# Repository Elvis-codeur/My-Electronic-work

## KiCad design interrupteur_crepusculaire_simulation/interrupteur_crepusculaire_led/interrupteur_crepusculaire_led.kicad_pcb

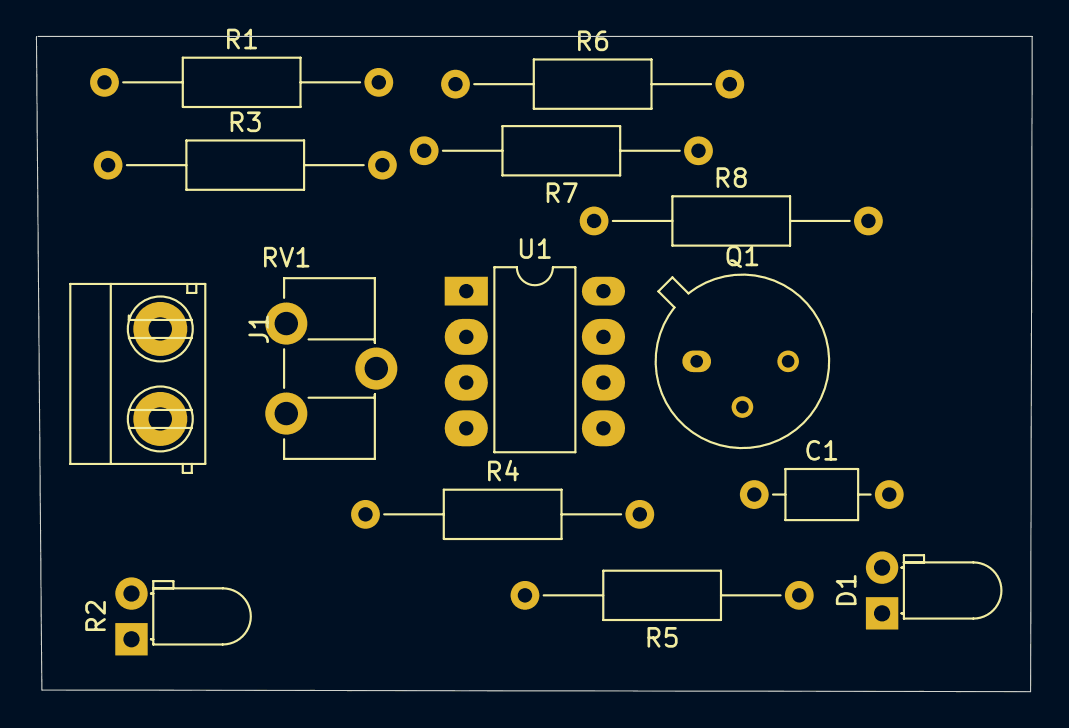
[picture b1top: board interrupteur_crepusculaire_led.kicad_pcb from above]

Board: 2 copper layers, 55.3 x 36.4 mm, 14 parts (0 on the bottom side), 8 nets, no tracks yet.

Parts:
C1: 10nF; C_Axial_L3.8mm_D2.6mm_P7.50mm_Horizontal
D1: LED; LED_D3.0mm_Horizontal_O1.27mm_Z2.0mm
J1: Entrée; Bornier_2pts_L10mm_W8mm_P5mm
Q1: 2N2219; TO-39-3
R1: 10K; R_Axial_DIN0207_L6.3mm_D2.5mm_P15.24mm_Horizontal
R2: LDR03; LED_D3.0mm_Horizontal_O1.27mm_Z2.0mm
R3, R4: 3.3K; R_Axial_DIN0207_L6.3mm_D2.5mm_P15.24mm_Horizontal
R5: 1M; R_Axial_DIN0207_L6.3mm_D2.5mm_P15.24mm_Horizontal
R6: 220R; R_Axial_DIN0207_L6.3mm_D2.5mm_P15.24mm_Horizontal
R7: 2.2K; R_Axial_DIN0207_L6.3mm_D2.5mm_P15.24mm_Horizontal
R8: 560R; R_Axial_DIN0207_L6.3mm_D2.5mm_P15.24mm_Horizontal
RV1: R_POT; Potentiometer_ACP_CA9-H5_Horizontal
U1: LM741; DIP-8_W7.62mm_LongPads

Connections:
GND: C1.2, D1.1, J1.2, R1.2, R2.2, R4.2, R7.2, U1.4
unnamed: Q1.2, R6.1, R7.1
unnamed: Q1.3, R8.2
unnamed: R2.1, U1.3
unnamed: R5.1, R6.2, U1.6
unnamed: RV1.2, U1.2
VCC: C1.1, J1.1, R1.1, R3.1, R8.1, U1.7
vs: D1.2, Q1.1

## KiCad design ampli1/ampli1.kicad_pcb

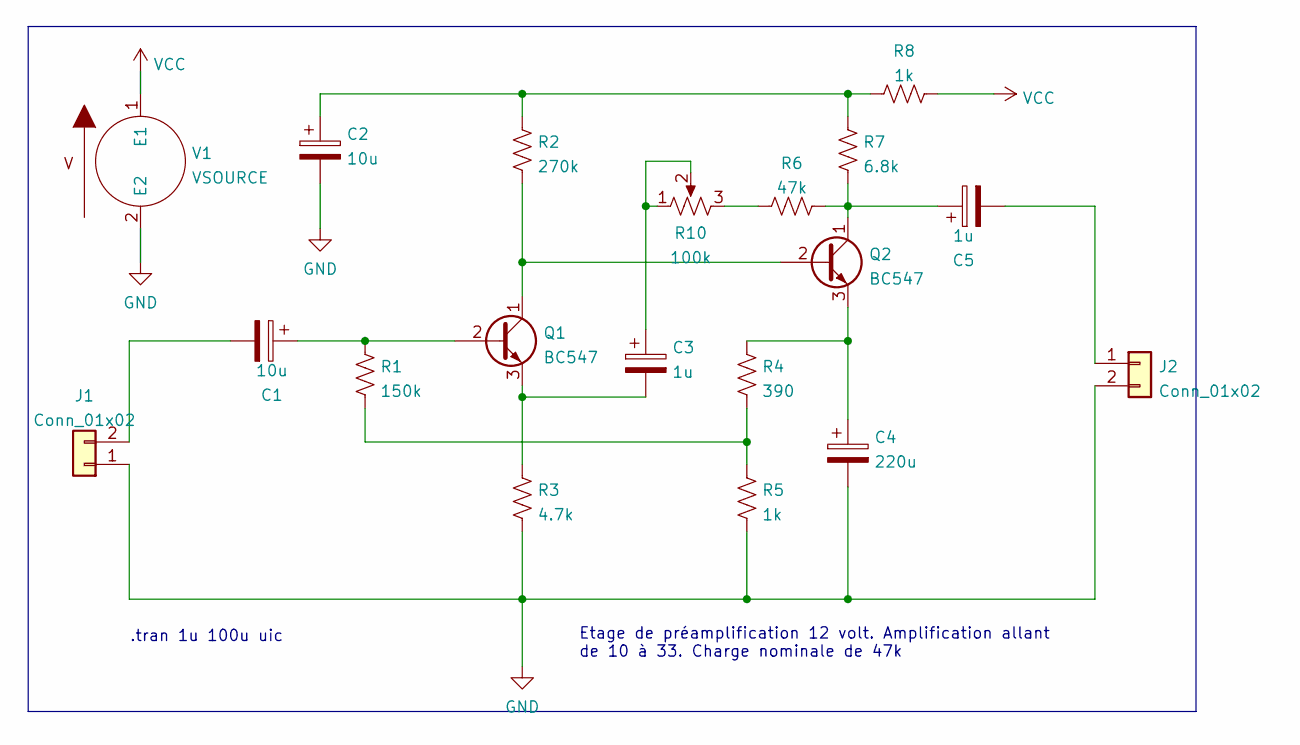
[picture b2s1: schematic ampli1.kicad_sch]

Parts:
C1, C2: 10u; CP_Radial_D10.0mm_P5.00mm
C3, C5: 1u; CP_Radial_D10.0mm_P5.00mm
C4: 220u; CP_Radial_D18.0mm_P7.50mm
J1, J2: Conn_01x02; PinSocket_1x02_P2.54mm_Vertical
Q1, Q2: BC547; TO-92_Inline
R1: 150k; R_Axial_DIN0207_L6.3mm_D2.5mm_P10.16mm_Horizontal
R2: 270k; R_Axial_DIN0207_L6.3mm_D2.5mm_P10.16mm_Horizontal
R3: 4.7k; R_Axial_DIN0207_L6.3mm_D2.5mm_P10.16mm_Horizontal
R4: 390; R_Axial_DIN0207_L6.3mm_D2.5mm_P10.16mm_Horizontal
R5, R8: 1k; R_Axial_DIN0207_L6.3mm_D2.5mm_P10.16mm_Horizontal
R6: 47k; R_Axial_DIN0207_L6.3mm_D2.5mm_P10.16mm_Horizontal
R7: 6.8k; R_Axial_DIN0207_L6.3mm_D2.5mm_P10.16mm_Horizontal
R10: 100k; Potentiometer_ACP_CA6-H2,5_Horizontal
V1: VSOURCE; PinSocket_1x02_P2.54mm_Vertical

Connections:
GND: C2.2, C4.2, J1.1, J2.2, R3.2, R5.2, V1.2 (E2)
unnamed: C1.1, Q1.2 (B), R1.1
unnamed: C1.2, J1.2
unnamed: C2.1, R2.1, R7.1, R8.2
unnamed 4: C3.1, R10.1, R10.2; also elsewhere on the board
unnamed: C3.2, Q1.3 (E), R3.1
unnamed: C4.1, Q2.3 (E), R4.1
unnamed: C5.1, Q2.1 (C), R6.2, R7.2
unnamed: C5.2, J2.1
unnamed: Q1.1 (C), Q2.2 (B), R2.2
unnamed: R1.2, R4.2, R5.1
unnamed 11: R6.1, R10.3; also elsewhere on the board
VCC: R8.1, V1.1 (E1)

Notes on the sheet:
Etage de préamplification 12 volt. Amplification allant de 10 à 33. Charge nominale de 47k
.tran 1u 100u uic

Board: 2 copper layers, 19 parts (0 on the bottom side), 13 nets, no tracks yet.

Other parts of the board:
RV1: 100k; Potentiometer_ACP_CA6-H2,5_Horizontal

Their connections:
unnamed 4: RV1.1, RV1.2; also elsewhere on the board
unnamed 11: RV1.3; also elsewhere on the board

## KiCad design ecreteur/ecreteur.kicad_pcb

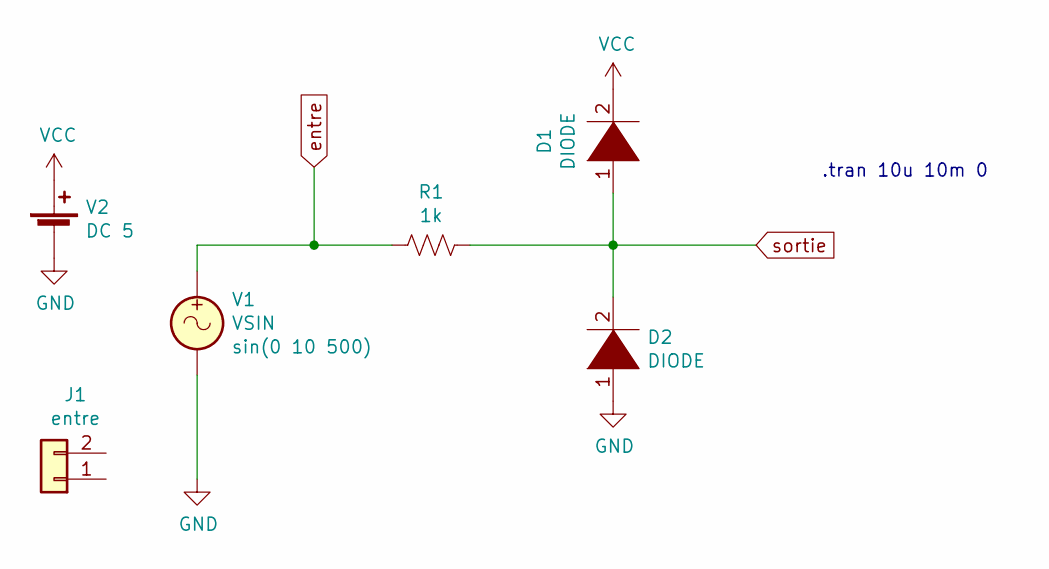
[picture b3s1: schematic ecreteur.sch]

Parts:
D1, D2: DIODE; R_Array_SIP4
J1: entre; R_Array_SIP4
R1: 1k; R_Array_SIP4
V1: VSIN; R_Array_SIP4
V2: DC 5; R_Array_SIP4

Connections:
GND: D2.1 (K), V1.2, V2.2 (-)
VCC: D1.2 (A), V2.1 (+)
entre: R1.2, V1.1
sortie: D1.1 (K), D2.2 (A), R1.1

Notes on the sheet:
.tran 10u 10m 0

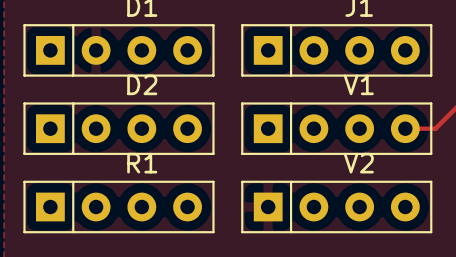
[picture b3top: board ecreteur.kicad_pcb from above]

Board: 2 copper layers, 6 parts (0 on the bottom side), 4 nets.

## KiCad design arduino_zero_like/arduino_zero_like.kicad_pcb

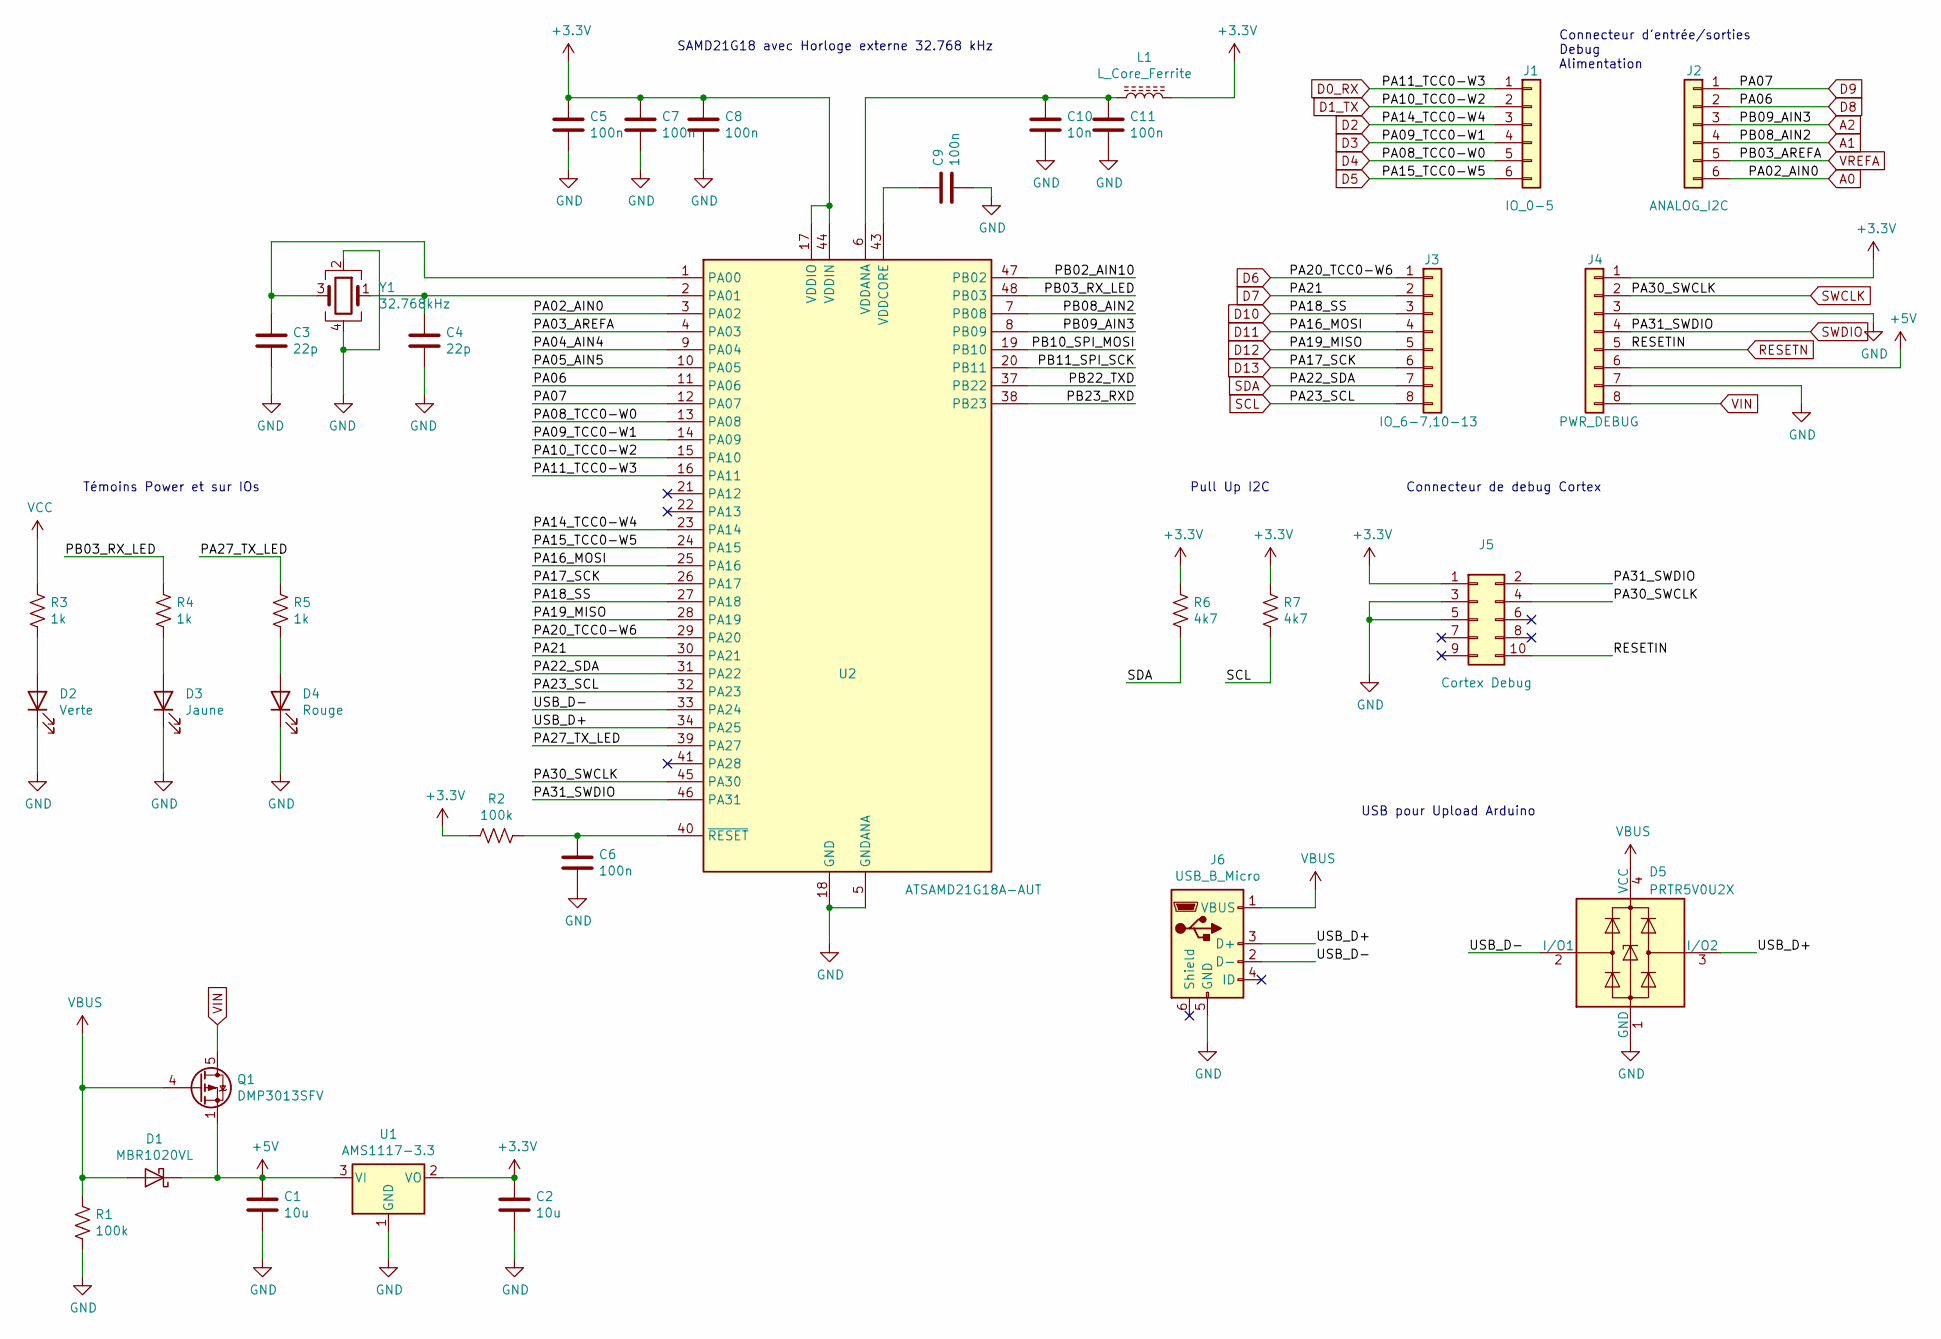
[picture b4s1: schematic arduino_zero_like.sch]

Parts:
C1: 10u; C_0402_1005Metric
C2: 10u; C_1206_3216Metric
C3, C4: 22p; C_0402_1005Metric
C5, C6, C7, C8, C9, C11: 100n; C_0402_1005Metric
C10: 10n; C_0402_1005Metric
D1: MBR1020VL; D_SOD-123
D2: Verte; LED_0603_1608Metric_Pad1.05x0.95mm_HandSolder
D3: Jaune; LED_0603_1608Metric_Pad1.05x0.95mm_HandSolder
D4: Rouge; LED_0603_1608Metric_Pad1.05x0.95mm_HandSolder
D5: PRTR5V0U2X; SOT-143
J1: IO_0-5; PinHeader_1x06_P2.54mm_Vertical
J2: ANALOG_I2C; PinSocket_1x06_P2.54mm_Vertical
J3: IO_6-7,10-13; PinSocket_1x08_P2.54mm_Vertical
J4: PWR_DEBUG; PinSocket_1x08_P2.54mm_Vertical
J5: Cortex Debug; PinHeader_1x05_P1.27mm_Vertical
J6: USB_B_Micro; USB_Micro-B_Wuerth_629105150521
L1: L_Core_Ferrite; L_0603_1608Metric_Pad1.05x0.95mm_HandSolder
Q1: DMP3013SFV; Diodes_PowerDI3333-8
R1, R2: 100k; R_0201_0603Metric
R3, R4, R5: 1k; R_0201_0603Metric
R6, R7: 4k7; R_0201_0603Metric
U1: AMS1117-3.3; SOT-223-3_TabPin2
U2: ATSAMD21G18A-AUT; TQFP-48_7x7mm_P0.5mm
Y1: 32.768kHz; Crystal_SMD_3225-4Pin_3.2x2.5mm

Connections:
+3V3: C2.1, C5.1, C7.1, C8.1, J4.1, J5.1, L1.2, R2.2, R6.1, R7.1, U1.2 (VO), U2.17 (VDDIO), U2.36 (VDDIO), U2.44 (VDDIN)
+5V: C1.1, D1.1 (K), J4.6, Q1.1 (S), Q1.2 (S), Q1.3 (S), U1.3 (VI)
/PA03_AREFA: U2.4 (PA03)
/PA04_AIN4: U2.9 (PA04)
/PA05_AIN5: U2.10 (PA05)
/PA27_TX_LED: R5.1, U2.39 (PA27)
/PB02_AIN10: U2.47 (PB02)
/PB03_RX_LED: R4.1, U2.48 (PB03)
/PB10_SPI_MOSI: U2.19 (PB10)
/PB11_SPI_SCK: U2.20 (PB11)
/PB22_TXD: U2.37 (PB22)
/PB23_RXD: U2.38 (PB23)
/USB_D+: D5.3 (I/O2), J6.3 (D+), U2.34 (PA25)
/USB_D-: D5.2 (I/O1), J6.2 (D-), U2.33 (PA24)
A0: J2.6, U2.3 (PA02)
A1: J2.4, U2.7 (PB08)
A2: J2.3, U2.8 (PB09)
D0_RX: J1.1, U2.16 (PA11)
D1_TX: J1.2, U2.15 (PA10)
D2: J1.3, U2.23 (PA14)
D3: J1.4, U2.14 (PA09)
D4: J1.5, U2.13 (PA08)
D5: J1.6, U2.24 (PA15)
D6: J3.1, U2.29 (PA20)
D7: J3.2, U2.30 (PA21)
D8: J2.2, U2.11 (PA06)
D9: J2.1, U2.12 (PA07)
D10: J3.3, U2.27 (PA18)
D11: J3.4, U2.25 (PA16)
D12: J3.5, U2.28 (PA19)
D13: J3.6, U2.26 (PA17)
GND: C1.2, C2.2, C3.2, C4.2, C5.2, C6.2, C7.2, C8.2, C9.2, C10.2, C11.2, D2.1 (K), D3.1 (K), D4.1 (K), D5.1 (GND), J4.3, J4.7, J5.3, J5.5, J6.5 (GND), R1.2, U1.1 (GND), U2.5 (GNDANA), U2.18 (GND), U2.35 (GND), U2.42 (GND), Y1.2, Y1.4
unnamed: C3.1, U2.1 (PA00), Y1.3
unnamed: C4.1, U2.2 (PA01), Y1.1
unnamed: C6.1, R2.1, U2.40 (~RESET)
unnamed: C9.1, U2.43 (VDDCORE)
unnamed: C10.1, C11.1, L1.1, U2.6 (VDDANA)
unnamed: D2.2 (A), R3.2
unnamed: D3.2 (A), R4.2
unnamed: D4.2 (A), R5.2
RESETN: J4.5, J5.10
SCL: J3.8, R7.2, U2.32 (PA23)
SDA: J3.7, R6.2, U2.31 (PA22)
SWCLK: J4.2, J5.4, U2.45 (PA30)
SWDIO: J4.4, J5.2, U2.46 (PA31)
VBUS: D1.2 (A), D5.4 (VCC), J6.1 (VBUS), Q1.4 (G), R1.1
VCC: R3.1
VIN: J4.8, Q1.5 (D)
VREFA: J2.5

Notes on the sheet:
SAMD21G18 avec Horloge externe 32.768 kHz
Connecteur de debug Cortex
Pull Up I2C
USB pour Upload Arduino
Témoins Power et sur IOs
Connecteur d'entrée/sorties Debug Alimentation

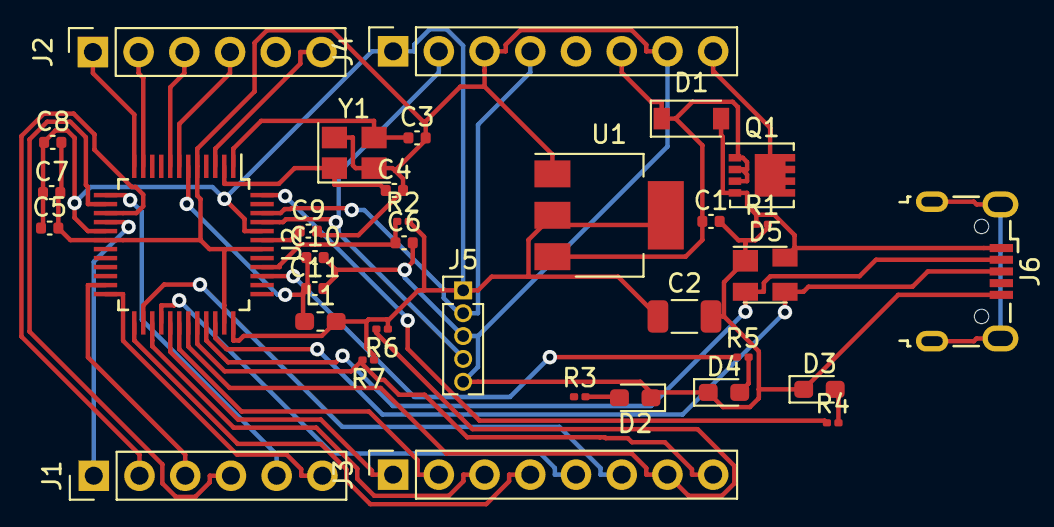
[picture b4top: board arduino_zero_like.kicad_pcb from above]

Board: 2 copper layers, 34 parts (0 on the bottom side), 38 nets.

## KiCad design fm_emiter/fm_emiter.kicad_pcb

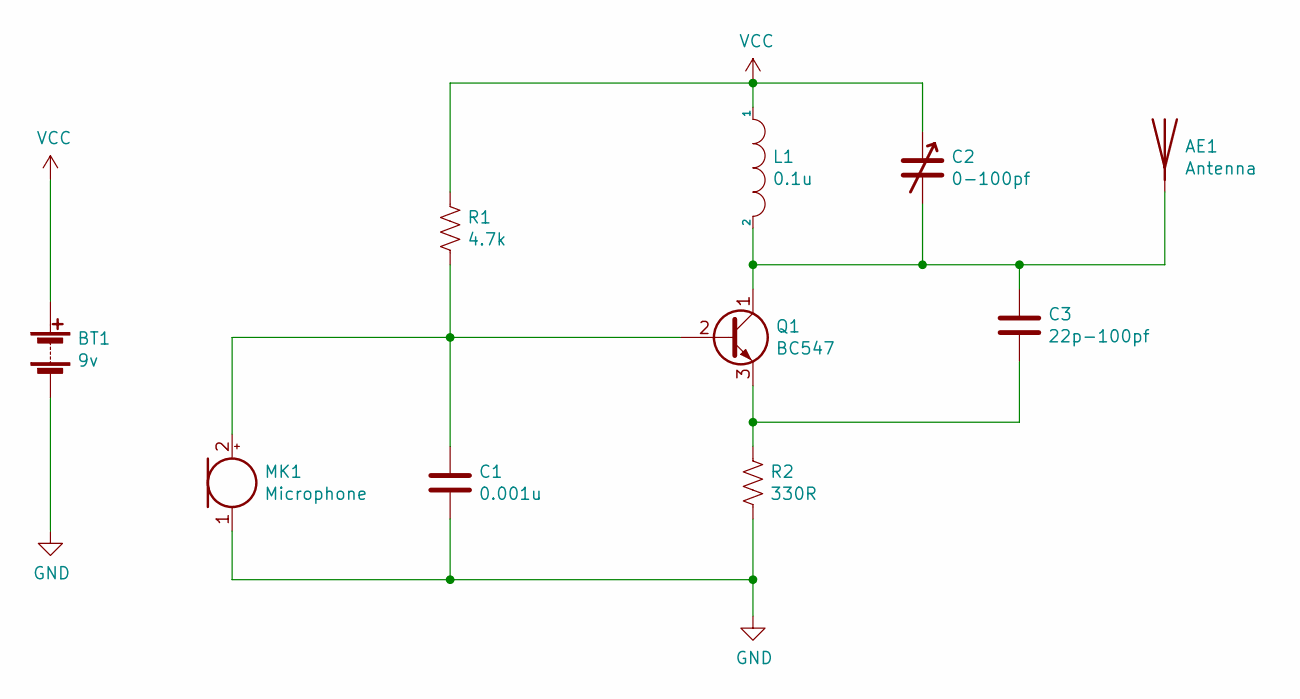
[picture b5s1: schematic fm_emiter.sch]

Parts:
AE1: Antenna; PinHeader_1x01_P1.00mm_Horizontal
BT1: 9v; PinSocket_1x02_P2.54mm_Vertical
C1: 0.001u; CP_Radial_D8.0mm_P5.00mm
C2: 0-100pf; CP_Axial_L18.0mm_D8.0mm_P25.00mm_Horizontal
C3: 22p-100pf; CP_Radial_Tantal_D5.0mm_P2.50mm
L1: 0.1u; L_Axial_L5.0mm_D3.6mm_P10.00mm_Horizontal_Murata_BL01RN1A2A2
MK1: Microphone; PinSocket_1x02_P2.54mm_Vertical
Q1: BC547; TO-92_Inline
R1: 4.7k; R_Axial_DIN0204_L3.6mm_D1.6mm_P5.08mm_Horizontal
R2: 330R; R_Axial_DIN0204_L3.6mm_D1.6mm_P5.08mm_Vertical

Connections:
GND: BT1.2 (-), C1.2, MK1.1 (-), R2.2
unnamed: AE1.1, C2.2, C3.1, L1.2, Q1.1 (C)
unnamed: C1.1, MK1.2 (+), Q1.2 (B), R1.2
unnamed: C3.2, Q1.3 (E), R2.1
VCC: BT1.1 (+), C2.1, L1.1, R1.1

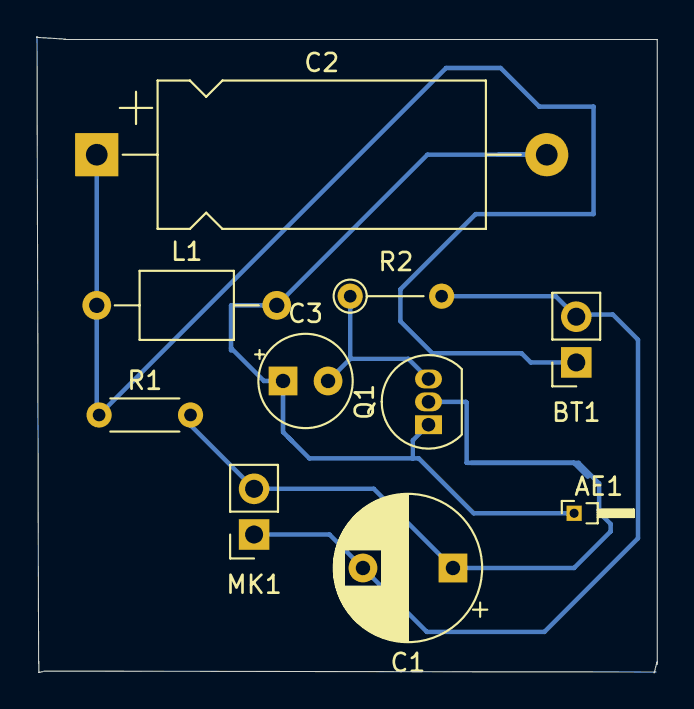
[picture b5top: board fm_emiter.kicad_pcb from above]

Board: 2 copper layers, 34.5 x 35.4 mm, 10 parts (0 on the bottom side), 5 nets.

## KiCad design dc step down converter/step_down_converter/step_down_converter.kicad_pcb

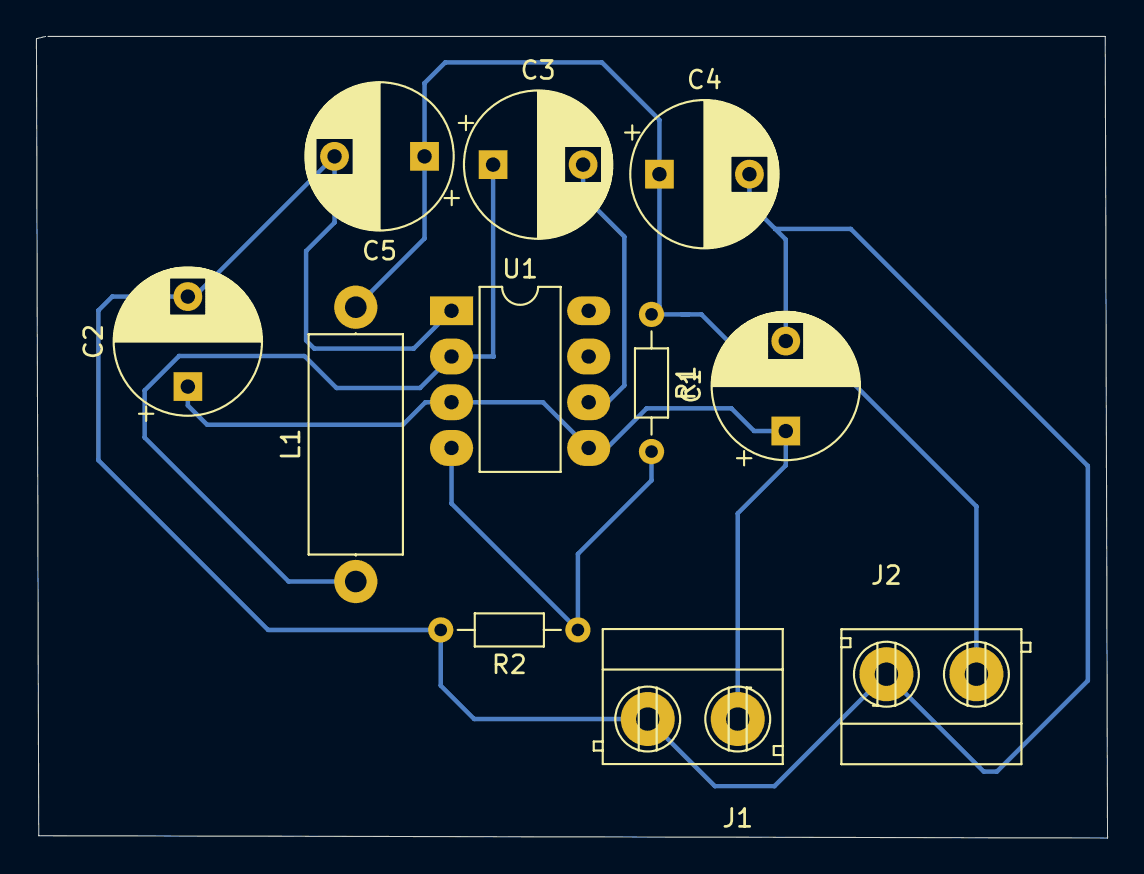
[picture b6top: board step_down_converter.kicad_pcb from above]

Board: 2 copper layers, 59.5 x 44.5 mm, 11 parts (0 on the bottom side), 6 nets.

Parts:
C1: 10uF; CP_Radial_D8.0mm_P5.00mm
C2, C3: 100nF; CP_Radial_D8.0mm_P5.00mm
C4, C5: 22uF; CP_Radial_D8.0mm_P5.00mm
J1: entrée; Bornier_2pts_L10mm_W8mm_P5mm
J2: Sortie; Bornier_2pts_L10mm_W8mm_P5mm
L1: 4.7uF; L_Axial_L12.0mm_D5.0mm_P15.24mm_Horizontal_Fastron_MISC
R1: 75; R_Axial_DIN0204_L3.6mm_D1.6mm_P7.62mm_Horizontal
R2: 10k; R_Axial_DIN0204_L3.6mm_D1.6mm_P7.62mm_Horizontal
U1: TPS565208; DIP-8_W7.62mm_LongPads

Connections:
GND: C1.2, C2.2, C4.2, C5.2, J1.2, J2.1, R2.2, U1.1
unnamed: C3.1, L1.1, U1.2
unnamed: C3.2, U1.6
unnamed: C4.1, C5.1, J2.2, L1.2, R1.1
unnamed: R1.2, R2.1, U1.4
VCC: C1.1, C2.1, J1.1, U1.3, U1.5

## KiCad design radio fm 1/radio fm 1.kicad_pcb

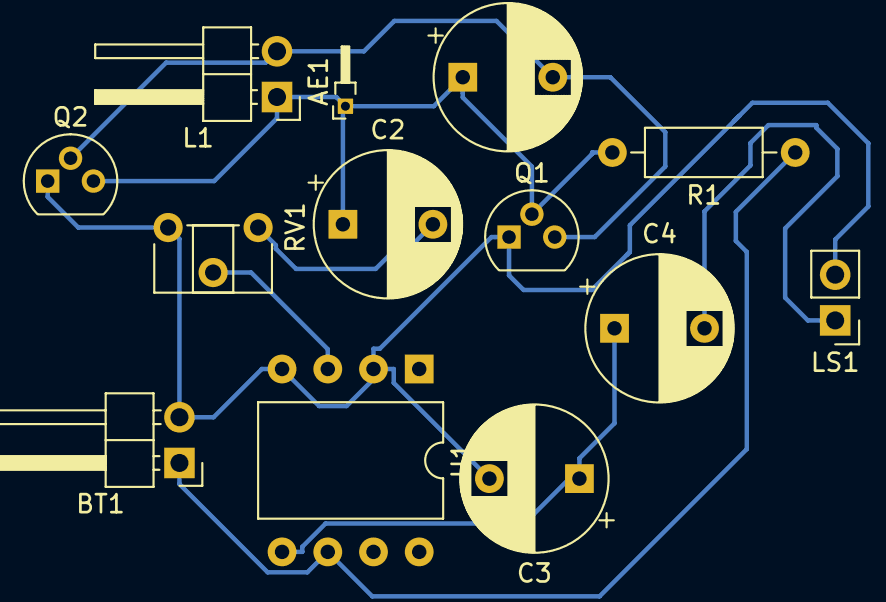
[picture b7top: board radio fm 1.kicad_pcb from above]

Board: 2 copper layers, 13 parts (0 on the bottom side), 8 nets.

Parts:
AE1: Antenna; PinHeader_1x01_P1.00mm_Horizontal
BT1: Battery; PinHeader_1x02_P2.54mm_Horizontal
C1: 22p; CP_Radial_D8.0mm_P5.00mm
C2: 0.22u; CP_Radial_D8.0mm_P5.00mm
C3: 0.1u; CP_Radial_D8.0mm_P5.00mm
C4: 220u; CP_Radial_D8.0mm_P5.00mm
L1: INDUCTOR; PinHeader_1x02_P2.54mm_Horizontal
LS1: Speaker; PinHeader_1x02_P2.54mm_Vertical
Q1, Q2: BF457; TO-92
R1: 22k; R_Axial_DIN0207_L6.3mm_D2.5mm_P10.16mm_Horizontal
RV1: 10k; Potentiometer_ACP_CA6-H2,5_Horizontal
U1: LM386; DIP-8_W10.16mm

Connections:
GND: BT1.2, C3.2, LS1.2, Q1.1, Q2.1, RV1.3, U1.2, U1.4
unnamed: AE1.1, C1.1, C2.1, L1.1, Q1.2, Q2.3, R1.2
unnamed: C1.2, L1.2, Q1.3, Q2.2
unnamed: C2.2, RV1.1
unnamed: C3.1, C4.1, U1.5
unnamed: C4.2, LS1.1
unnamed: RV1.2, U1.3
VCC: BT1.1, R1.1, U1.6

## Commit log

2023-01-26 Premier commit du 26/01/2023
